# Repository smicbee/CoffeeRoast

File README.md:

# CoffeeRoast

We built a coffee roaster from a popcorn machine by adding temperature control. It follows a reproducible roast curve.

## Used Components

**Microcontroller:** LilyGo T-Display S3 ESP32-S3 (probably overkill, but it has a nice display and WiFi functionality if needed)  
From: [Amazon](https://www.amazon.de/LILYGO-T-Display-S3-Entwicklungsboard-Normalbildschirm-schwarzem/dp/B0BRTT727Z?source=ps-sl-shoppingads-lpcontext&ref_=fplfs&smid=ANWK9D8XV9DLB&th=1)

**Popcorn Maker:** [Severin Popcorn-Maker](https://popcorn-rezepte.de/severin-pc-3751-popcornautomat-weiss-heissluft)  
From: Ebay/Kleinanzeigen for 5-10€. People often get this as a gift, use it once or not at all, and then sell it on eBay.

**Temperature Sensor:** MAX6675 Temperature Sensor, K Type  
From: [Amazon](https://www.amazon.de/dp/B0DFM7SJ3Z?ref=ppx_yo2ov_dt_b_fed_asin_title)

**Solid State Relay:** Solid-State-Relay SSR-40DA  
From: [Amazon](https://www.amazon.de/dp/B0CDKCBJRT?ref=ppx_yo2ov_dt_b_fed_asin_title)

Cables, drills, screwdriver, soldering iron

## Instructions

To modify the roaster, we had to:
* Add a temperature sensor
* Add a solid-state relay to the heater
* Add a PWM transistor to the fan

First, we took apart the popcorn maker. It basically consists of two elements: heating coils and a fan for the air.  
These popcorn makers are engineered to the limit, so please be gentle with them as they are made of a lot of plastic. We destroyed a couple until we got it right. Even then, the plastic melted on the third continuous roast.

The main power switch connects the 230V from the outlet directly to the heating coils. The fan is connected to the heating coil in a way that ~24V AC goes through a rectifier (4 diodes) and is converted from AC to DC.

In the first step, we needed to decouple the heating coils from the fan and make the heating coil controllable using our solid-state relay. We disconnected the fan from the diodes so we could run it from an external power supply providing 24V later on.  
The heating coil was then soldered directly to the neutral conductor (blue wire). The red wire was cut, and the solid-state relay was installed in between so we could control the power of the heating element using PWM later.

An external or lab power supply was used to provide 24V DC to the fan, so it runs permanently. The fan can take from 4V to 30V. We can adjust the voltage to control the speed or later use a GPIO, a diode, and a transistor to control it from the ESP32. The ESP ensures a smooth start of the fan. We broke one of the fans due to rapid spin up/down.

We drilled a hole in the top metal container to fit the thermocouple inside the roasting chamber.  
**Note:** If the temperature sensor touches the metal casing, it won't work properly. We insulated the sensor with Kapton tape or a non-conductive washer. The temperature reading is 0°C if the motor is spinning and no insulation was used. This is handled by the code to be filtered out, but the roaster will go into fail-safe mode after 30s of nonsensical temperature readings and spin up the fan to 100%.

The other 4 pins go into the ESP32 (VCC = 5V, GND = Ground, CLK = GPIO_13, CS = GPIO_12, DO = GPIO_11).

Also, the solid-state relay is connected to the ESP32. In our case, the voltage provided by the GPIO was sufficient to control the solid-state relay, so we controlled it directly via the GPIO. If this does not work, you will need a separate transistor and a 5V supply for the SSR.  
The SSR uses GPIO_1 in our setup.

## Control Box

We 3D printed a box containing:
* ESP32
* 24V Fan PWM control
* SSR (solid-state relay) control
* Temperature sensor readout board

And that's it!

Initially, we wanted to use the ESP32 with Artisan (the software used for commercial products, e.g., Coffeelogic Nano), but we had no luck getting it to work with a PID. So, we decided to write our own software using C#. Communication is done via simple serial commands.  
You can send "get temp" via serial to the ESP32, and it will respond with the current temperature from the thermocouple.  
You can also send "set setpoint 255", which the ESP32 interprets to set the PWM duty cycle to 100% (255 = 100%, 128 = 50%, 0 = 0%).  
The firmware clamps `set setpoint` and `set fan` commands to the 0-255 PWM range and supports `get status` for a compact controller health line with state, temperature, heater, fan, fan target, and thermocouple error count.
The C# application can be found in the iRoastControl folder.

# Example Usage

Use no more than 100g of beans and roast in a well-ventilated area. Prepare for coffee skins flying _everywhere_.  
You can stop the roast at any time by flipping the on-off switch, which effectively disconnects the heater while keeping the cooling fan running.

[12s_roast.webm](https://github.com/user-attachments/assets/c60a7ab9-1068-4cd1-9d56-9880ee272cc1)

[12s video of 12min roasting](docu/assets/img/rel/12s_roast.webm)

# CoffeeRoast V2 Web

Die neue Steuerungsoberfläche liegt unter [`CoffeeRoast V2/`](CoffeeRoast%20V2/) und ist als moderne, responsive Webanwendung umgesetzt.

- Live-Verbindung zum bestehenden ESP32 über die Web Serial API
- vorhandenes serielles Protokoll und alle `.kpro`-Rezepte bleiben nutzbar
- Safety-Preflight, Failsafe, Vorheizen, Rösten und Abkühlen
- eingebauter Simulator, Canvas-Live-Plot und CSV-Export
- öffentlich bereitgestellt unter **https://coffeeroast.michaelbeetz.de/**

Für die USB-Verbindung wird Chrome oder Edge benötigt. Der Browser spricht direkt mit dem lokal ausgewählten USB-Gerät; der Webserver erhält keinen Zugriff auf den Controller.

# iRoastControl (Legacy)

iRoastControl is the control software. It comes with predefined roast curves you can use for your first roast.

## Build and Run on Windows

iRoastControl is a Windows Forms application for .NET Framework 4.7.2. Build it with Visual Studio 2022 and the ".NET desktop development" workload installed, including the .NET Framework 4.7.2 targeting pack or developer pack.

1. Connect the ESP32 roaster controller to the Windows PC over USB and confirm it appears as a COM port.
2. Open `iRoastControl Software/iRoastControl.sln` in Visual Studio.
3. Restore NuGet packages when Visual Studio prompts you, or use **Build > Restore NuGet Packages** before the first build. The project uses `packages.config`, so packages are restored into a repository-level `packages` folder.
4. Build the `Debug|Any CPU` or `Release|Any CPU` configuration, then press **Start** in Visual Studio or run the generated `iRoastControl.exe` from `iRoastControl Software/bin/Debug/` or `iRoastControl Software/bin/Release/`.

On startup the application scans available COM ports at `115200` baud, 8 data bits, no parity, one stop bit, and no handshake. It sends `hello` and expects the ESP32 firmware to answer `popcorn roaster`; after that it sends commands such as `get temp`, `set setpoint <0-255>`, and `set fan <0-255>`. If the app does not connect, check that the ESP32 firmware is running, no serial monitor has the port open, and the USB driver exposes the board as a COM port.

Roast recipes are loaded from the `Recipes` folder next to the running application. The source recipes live in `iRoastControl Software/Recipes/*.kpro` and are copied to the build output during the Visual Studio build. Add custom `.kpro` files to that folder before building, or copy them into `bin/Debug/Recipes/` or `bin/Release/Recipes/` beside the executable.

## First-Run Calibration and Safety Check

Before the first heated run, flash the ESP32 firmware, start iRoastControl, and leave the chamber empty. When you press "Run" from idle, the application requests `get status` from the controller and shows a preflight checklist. Confirm only after the thermocouple is insulated from the metal chamber, the fan moves air freely, the SSR is wired through the controller, ventilation is running, and the manual power cut-off is reachable.

Each roasting curve has three phases: pre-heating, running, and cool-down. When you click "Run" the first time, the application pre-heats the empty popcorn machine until the thermocouple reaches 180°C. This is when you add your coffee beans. After that, press "Run" again and the button will turn yellow. This is where the roasting curve starts. You can follow your roasting temperatures by watching the red graph. Pressing the "Run" button again will abort and start the cool-down phase, where the heating element turns off and only the fan runs. When the temperature drops below 60°C, the app returns to idle.

If the thermocouple returns repeated impossible readings, the firmware enters failsafe, turns the heater off, and drives the fan to 255/255. The app also treats a controller status containing `failsafe` as a blocked start until the wiring or sensor issue is fixed.

## UI

At the moment, the curves are defined by some points in the source code, which get interpolated using a CubicSpline function. You can find the key points in `ControlClass.cs` in the function `generateDefaultCurve()`. Each point describes the temperature depending on the time in seconds, e.g., `targetPoints.Add(new PointF(660, 180));` means at 660s of the roasting curve, we should reach 180°C.  
Adjust as you like.

# Fails

If the popcorn maker is old (like 20 years), the fan blades are rather brittle and may break easily if used on full power.

**Note:** If the temperature sensor touches the metal casing, it won't work properly. We recommend insulating the sensor with Kapton tape or a non-conductive washer.

# Tips

* Cover any holes on top with Kapton tape to retain heat better. Plastic might melt a bit, though.
* Test the roast with actual popcorn, as it's cheaper if anything goes wrong.
* Experiment and change only one setting at a time.

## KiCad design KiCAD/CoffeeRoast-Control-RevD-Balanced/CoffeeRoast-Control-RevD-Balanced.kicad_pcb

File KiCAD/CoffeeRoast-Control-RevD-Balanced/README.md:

# CoffeeRoast Control RevD Balanced — final routed candidate

RevD is a **separate final routed candidate** derived from the exact RevC UltraCompact circuit and footprints. It keeps the **96 × 60 mm, two-layer** board outline but distributes the functional blocks more evenly over the usable area.

The proven RevC project remains untouched.

## What changed

- Thermocouple/MAX6675 block moved upward and opened out.
- SSR and fan-driver support parts use more of the centre-left area instead of crowding the bottom edge.
- RESET/BOOT controls and probes have clearer service access.
- USB-C remains on the top edge. J5 is rotated 180° so the XKB `Product Edge`/mating face is exactly at board `y = 0`; the fine SMT tail row is inboard at `y = 7.345 mm`. Field wiring remains grouped along the bottom edge.
- ESP32-S3-WROOM-1 moved to the top edge; the physical antenna front is exactly flush with `y = 0`.
- The on-board antenna keepout is now **48 × 6.2 mm**: Espressif's 18 × 6.2 mm antenna area plus conservative 15 mm side clearances; forward clearance lies outside the PCB.
- Buck converter moved upward into the recovered right-hand area.
- SSR, ESC/PWM, fan and 24 V field pads are distributed farther apart along the bottom edge.
- Front and back silkscreen identify the functional blocks, including USB/ESD, MAX6675 thermocouple front-end, SSR driver, 10 V gate supply, fan driver/MOSFET, ESP32-S3, antenna keepout and 24 V-to-3.3 V buck stage.
- Three compact, unpopulated 1.27 mm headers reserve the future local user interface without changing firmware:
  - `J7` digital microphone: 3V3, GND, BCLK, WS, DATA, SEL;
  - `J8` I2C LCD: 3V3, GND, SDA, SCL, INT, RST;
  - `J9` four-button panel: GND, BTN1, BTN2, BTN3, BTN4, optional 3V3.
- All three future UI connectors are explicitly 3.3 V interfaces. They are hardware reservations only; pin initialization, I2S/I2C drivers, pull-ups and button handling are not implemented in software yet.
- J7–J9 now use horizontal pad rows. Every pin function is printed immediately beside its pad with 90-degree text on both board sides, and each complete MIC/LCD/BUTTONS group is enclosed by its own silkscreen frame.
- Board remains SELV/low voltage only; 230 VAC stays outside the PCB.

## Final verification state

RevD is fully routed as a reproducible two-layer manufacturing candidate:

- board outline: **96 × 60 mm**
- copper layers: **F.Cu + B.Cu only**
- full routed DRC: **0 violations**
- unconnected items: **0**
- schematic ERC: **0 violations**
- schematic/PCB parity: **0 issues**
- orientation/polarity audit: **PASS, 32 functional references asserted**
- routing angle audit: **0 non-45°/90° segments**
- `+24V_RAW` and `FAN_NEG`: **1.0 mm throughout, no vias**
- USB D+/D- total-length skew: **5.694 mm** (short USB Full-Speed path; electrically negligible timing skew)
- top/bottom/combined routing renders: `render/final-routing/`
- detailed audit: `docs/orientation_and_mechanical_audit.md`

The local fabrication package is generated under `production/partial-smd-pcba/` and contains Gerber, drill, BOM, CPL, DNP/HAND lists and zero-finding QA reports. It is locally order-ready, but checkout remains blocked until the live assembler preview confirms package identity, Pin 1/polarity, placement, current stock and enclosure fit.

## Reproduce and verify the final route

From this directory with KiCad/pcbnew 9.0.8:

```bash
python3 -m pip install -r tools/requirements.txt
python3 tools/add_ui_connectors_to_schematic.py
/usr/bin/python3 tools/build_balanced_revd.py
/usr/bin/python3 tools/finalize_routing.py
/usr/bin/python3 tools/audit_orientation_sensitive_parts.py
/usr/bin/python3 tools/audit_final_routing.py
kicad-cli pcb drc --severity-all --format json \
  --all-track-errors --schematic-parity \
  -o qa/placement-ui-parity-drc.json CoffeeRoast-Control-RevD-Balanced.kicad_pcb
kicad-cli sch erc --format json \
  -o qa/erc-ui.json CoffeeRoast-Control-RevD-Balanced.kicad_sch
/usr/bin/python3 tools/render_routing_preview.py
/usr/bin/python3 tools/prepare_partial_pcba_package.py
```

The final-routing script is idempotent by default once revision `D-FINAL` is present. Pass `--force` only for a deliberate full regeneration. It uses the SHA-256-pinned Freerouting 2.2.4 engine, pre-routes the fine-pitch USB VBUS and MCU-side D+ constraints, preserves 1.0 mm critical-current classes, removes exact SES duplicates, adds both GND planes and marks the result `D-FINAL`.

The detailed UI pin map, including physical pad coordinates, is in `docs/ui_expansion_connectors.csv`. The 1.27 mm headers remain `HAND/DNP` placeholders until the display, microphone module and enclosure cable scheme are selected.

## Electrical simulation

A reproducible block-level electrical simulation is in `sim/`. It covers the 24 V-to-3.3 V buck power stage, feedback corners, fan MOSFET loss, 10 V gate-supply budget, 24 V PSU loading, input bulk capacitance, USB CC current and an external SSR-input sweep. See `sim/README.md` for results and explicit model limits.

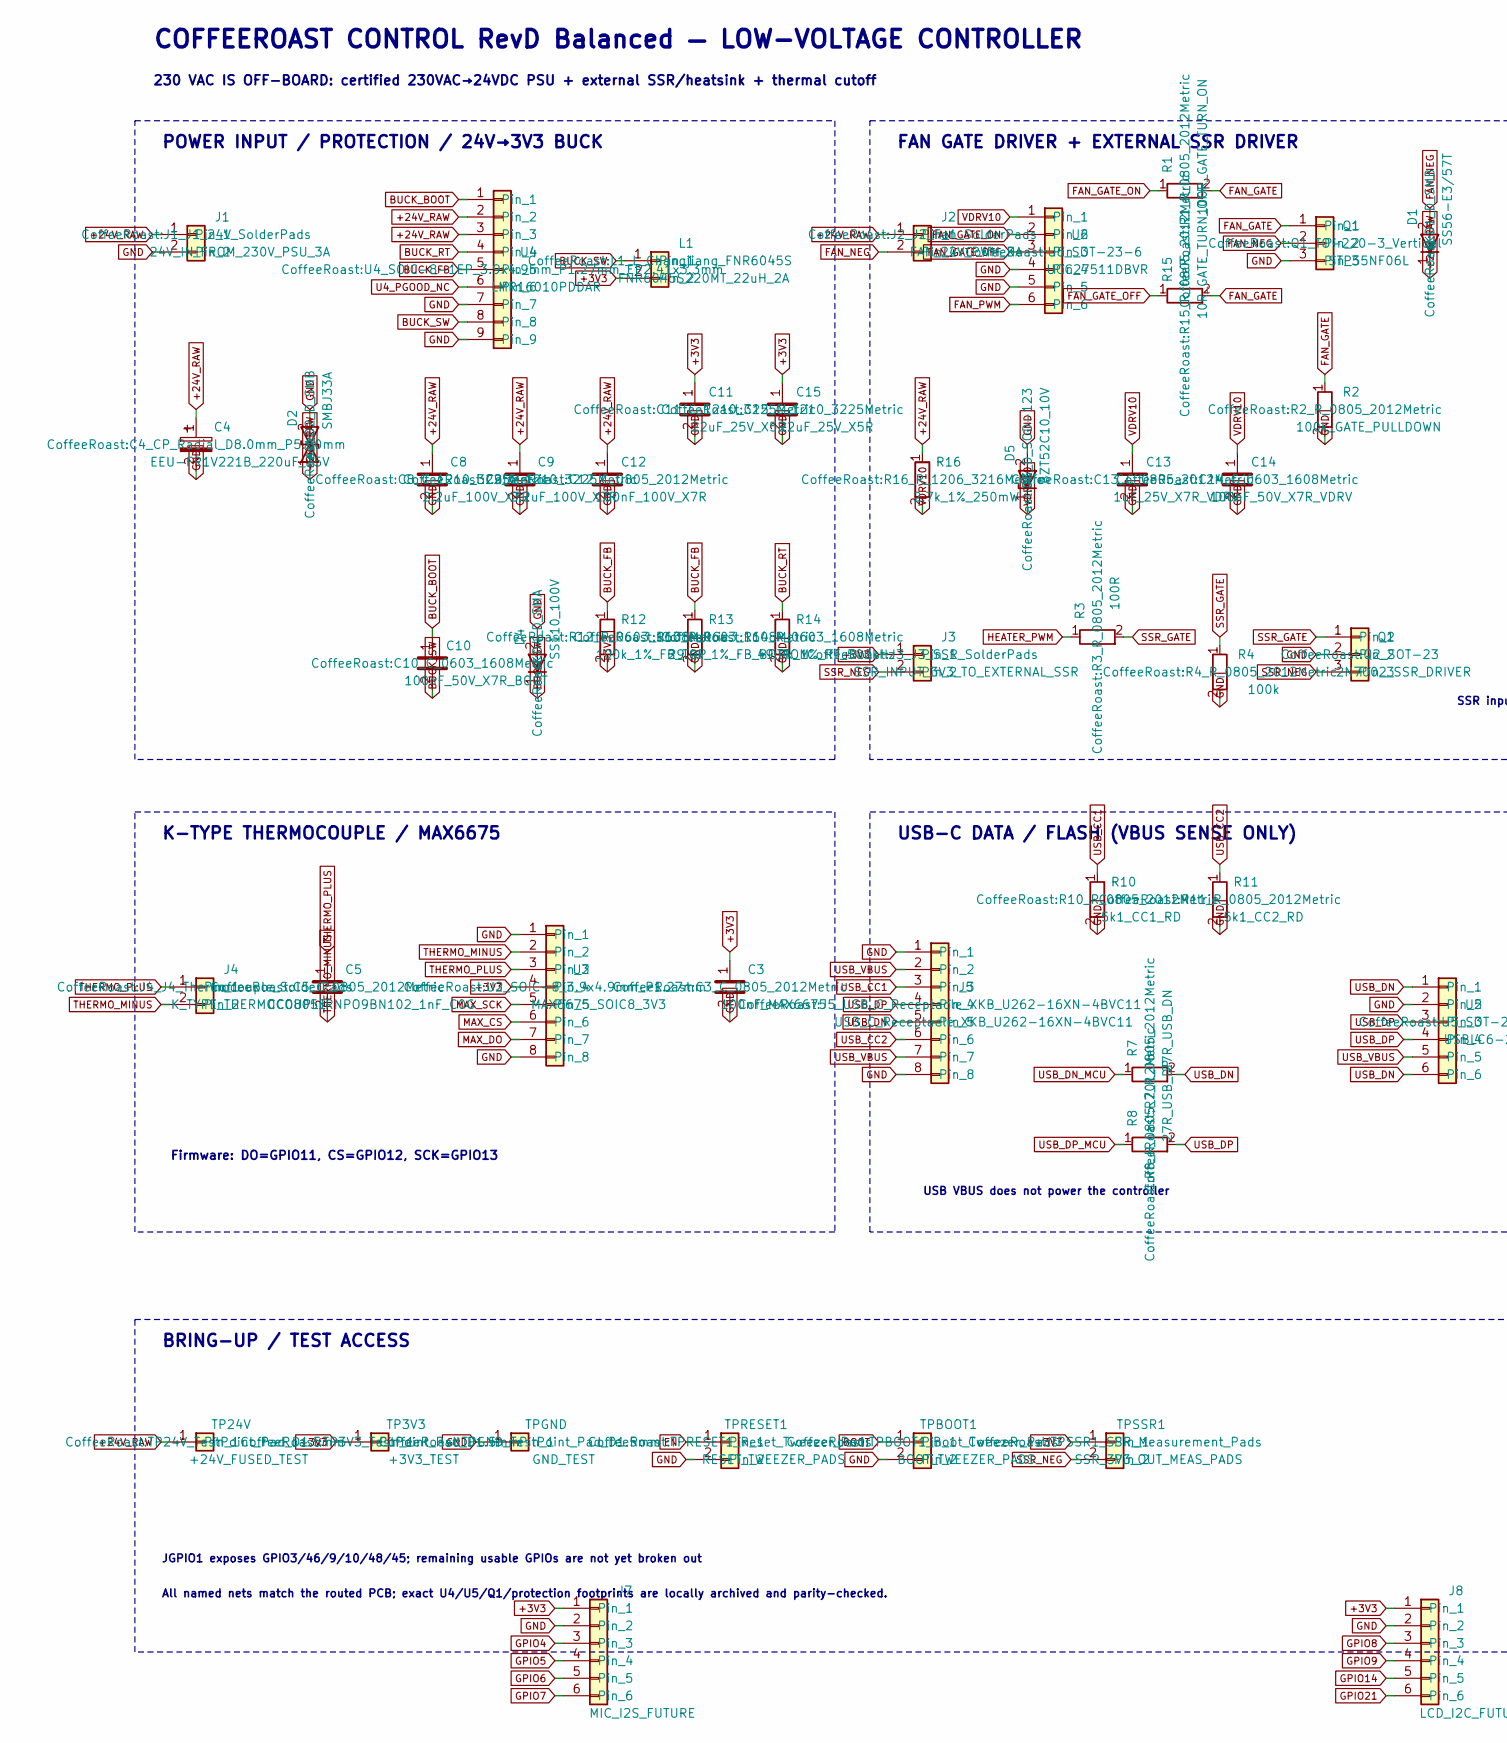
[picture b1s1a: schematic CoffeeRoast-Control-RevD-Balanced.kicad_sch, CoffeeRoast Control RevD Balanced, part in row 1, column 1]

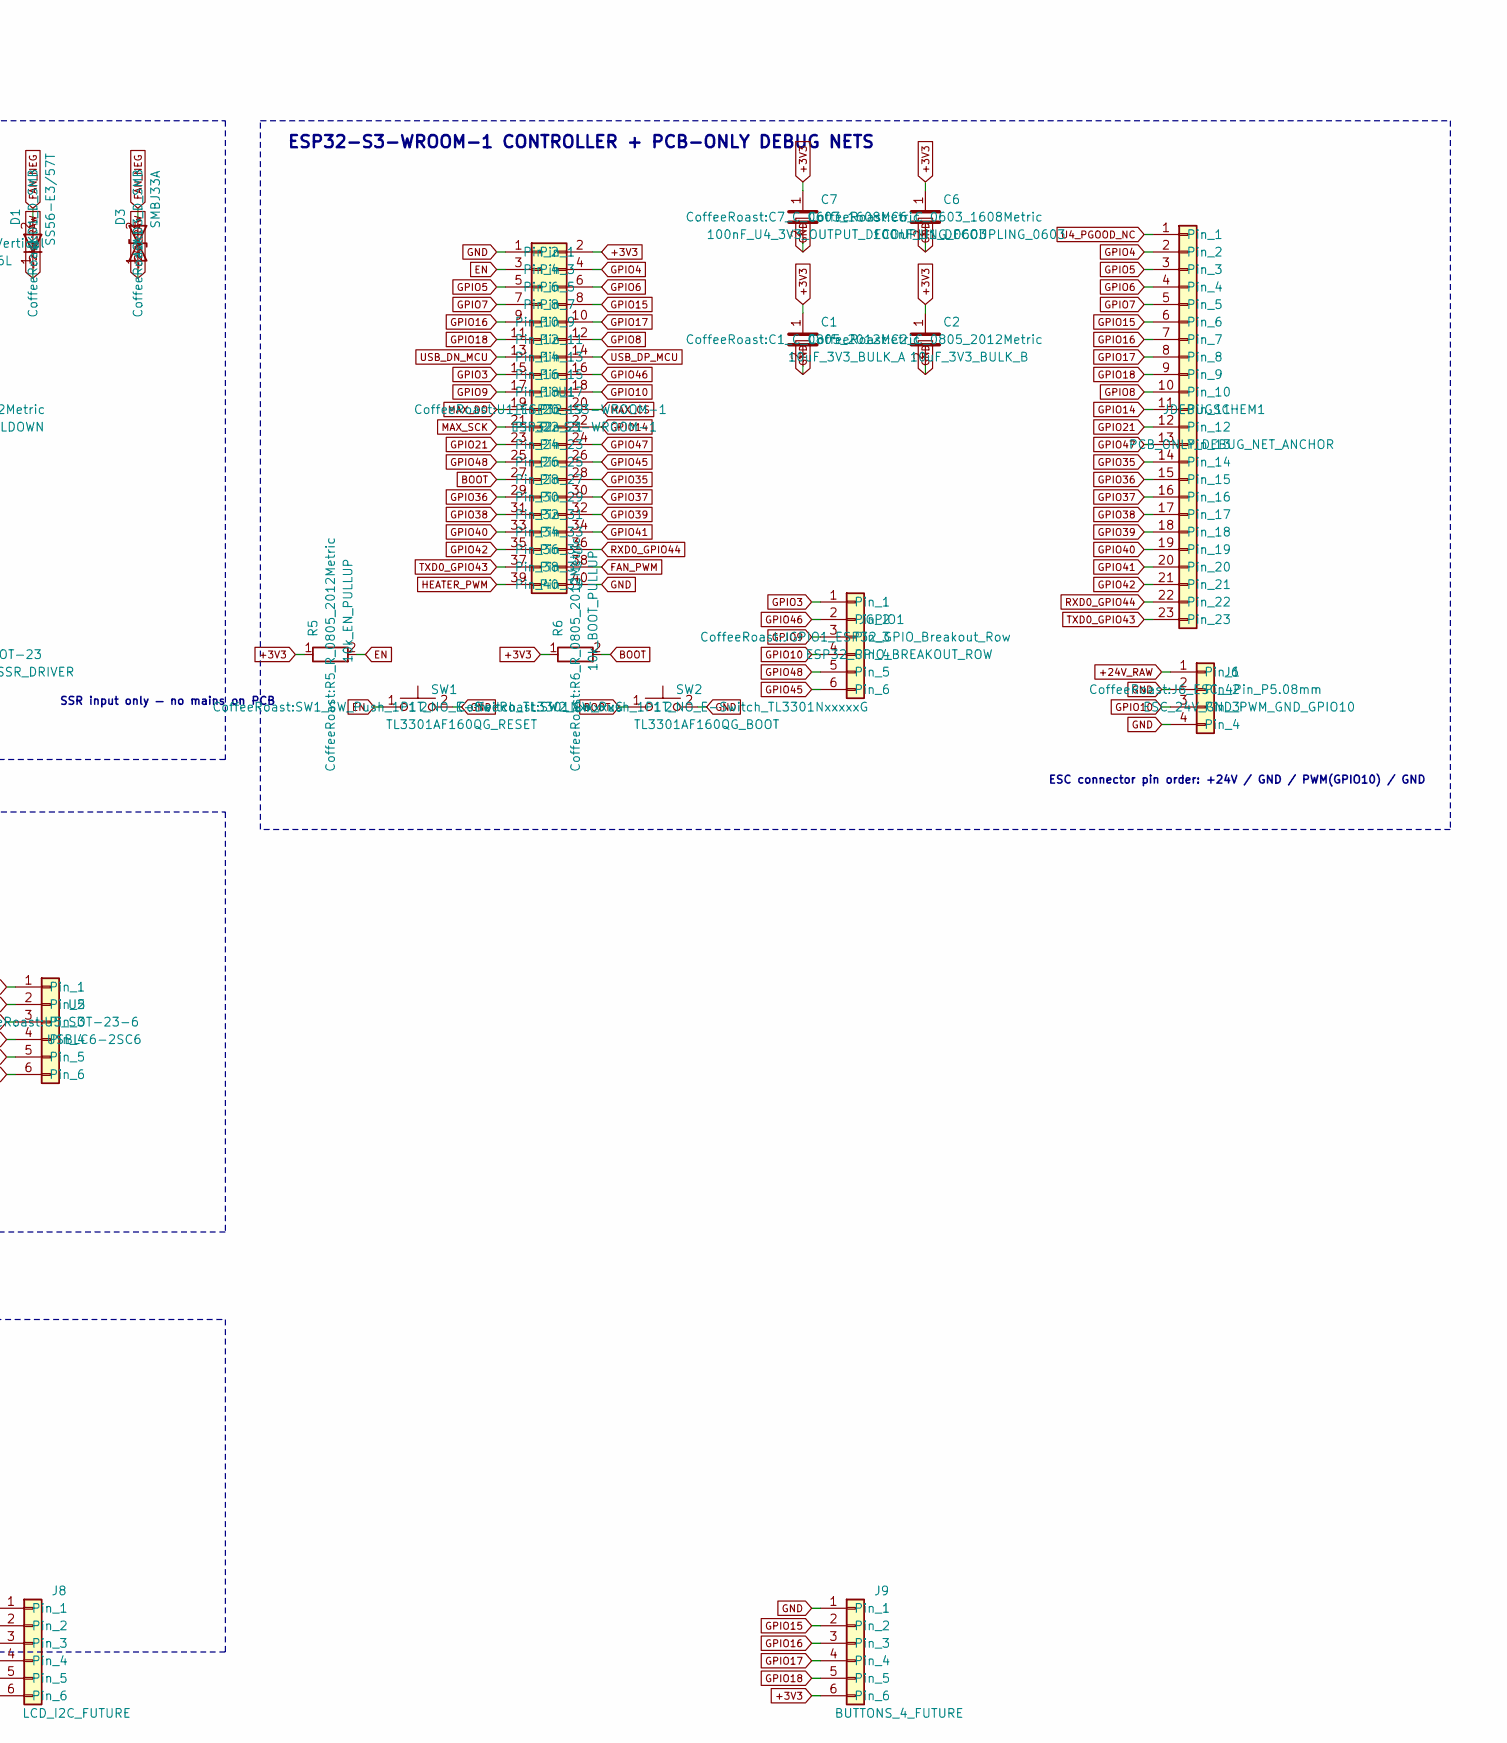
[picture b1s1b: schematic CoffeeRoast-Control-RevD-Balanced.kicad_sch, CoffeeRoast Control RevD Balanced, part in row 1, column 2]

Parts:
C1: 10uF_3V3_BULK_A; C1_C_0805_2012Metric
C2: 10uF_3V3_BULK_B; C2_C_0805_2012Metric
C3: 100nF_MAX6675; C3_C_0805_2012Metric
C4: EEU-FR1V221B_220uF_35V; C4_CP_Radial_D8.0mm_P5.00mm
C5: CC0805JRNPO9BN102_1nF_C0G; C5_C_0805_2012Metric
C6: 100nF_U1_DECOUPLING_0603; C6_C_0603_1608Metric
C7: 100nF_U4_3V3_OUTPUT_DECOUPLING_0603; C7_C_0603_1608Metric
C8: 2.2uF_100V_X7R; C8_C_1210_3225Metric
C9: 2.2uF_100V_X7R; C9_C_1210_3225Metric
C10: 100nF_50V_X7R_BOOT; C10_C_0603_1608Metric
C11: 22uF_25V_X5R; C11_C_1210_3225Metric
C12: 100nF_100V_X7R; C12_C_0805_2012Metric
C13: 1uF_25V_X7R_VDRV; C13_C_0805_2012Metric
C14: 100nF_50V_X7R_VDRV; C14_C_0603_1608Metric
C15: 22uF_25V_X5R; C15_C_1210_3225Metric
D1: SS56-E3/57T; D1_D_SMB
D2: SMBJ33A; D2_D_SMB
D3: SMBJ33A; D3_D_SMB
D4: SS110_100V; D4_D_SMA
D5: BZT52C10_10V; D5_D_SOD-123
J1: 24V_IN_FROM_230V_PSU_3A; J1_J1_24V_SolderPads
J2: FAN_24V_PWM_3A; J2_J2_Fan_SolderPads
J3: SSR_INPUT_3V3_TO_EXTERNAL_SSR; J3_J3_SSR_SolderPads
J4: K_TYPE_THERMOCOUPLE; J4_J4_Thermocouple_SolderPads
J5: USB_C_Receptacle_XKB_U262-16XN-4BVC11; J5_USB_C_Receptacle_XKB_U262-16XN-4BVC11
J6: ESC_24V_GND_PWM_GND_GPIO10; J6_ESC_4Pin_P5.08mm
J7: MIC_I2S_FUTURE; PinHeader_1x06_P1.27mm_Vertical
J8: LCD_I2C_FUTURE; PinHeader_1x06_P1.27mm_Vertical
J9: BUTTONS_4_FUTURE; PinHeader_1x06_P1.27mm_Vertical
JDEBUGSCHEM1: PCB_ONLY_DEBUG_NET_ANCHOR
JGPIO1: ESP32_GPIO_BREAKOUT_ROW; JGPIO1_ESP32_GPIO_Breakout_Row
L1: FNR6045S220MT_22uH_2A; L1_L_Changjiang_FNR6045S
Q1: STP55NF06L; Q1_TO-220-3_Vertical
Q2: 2N7002_SSR_DRIVER; Q2_SOT-23
R1: 100R_GATE_TURN_ON; R1_R_0805_2012Metric
R2: 100k_GATE_PULLDOWN; R2_R_0805_2012Metric
R3: 100R; R3_R_0805_2012Metric
R4: 100k; R4_R_0805_2012Metric
R5: 10k_EN_PULLUP; R5_R_0805_2012Metric
R6: 10k_BOOT_PULLUP; R6_R_0805_2012Metric
R7: 27R_USB_DN; R7_R_0805_2012Metric
R8: 27R_USB_DP; R8_R_0805_2012Metric
R10: 5k1_CC1_RD; R10_R_0805_2012Metric
R11: 5k1_CC2_RD; R11_R_0805_2012Metric
R12: 100k_1%_FB_TOP; R12_R_0603_1608Metric
R13: 29.4k_1%_FB_BOTTOM; R13_R_0603_1608Metric
R14: 49.9k_1%_RT_500kHz; R14_R_0603_1608Metric
R15: 10R_GATE_TURN_OFF; R15_R_0805_2012Metric
R16: 2.7k_1%_250mW; R16_R_1206_3216Metric
SW1: TL3301AF160QG_RESET; SW1_SW_Push_1P1T_NO_E-Switch_TL3301NxxxxxG
SW2: TL3301AF160QG_BOOT; SW2_SW_Push_1P1T_NO_E-Switch_TL3301NxxxxxG
TP3V3: +3V3_TEST; TP3V3_TestPoint_Pad_D1.5mm
TP24V: +24V_FUSED_TEST; TP24V_TestPoint_Pad_D1.5mm
TPBOOT1: BOOT_TWEEZER_PADS; TPBOOT1_Boot_Tweezer_Pads
TPGND: GND_TEST; TPGND_TestPoint_Pad_D1.5mm
TPRESET1: RESET_TWEEZER_PADS; TPRESET1_Reset_Tweezer_Pads
TPSSR1: SSR_3V3_OUT_MEAS_PADS; TPSSR1_SSR_Measurement_Pads
U1: ESP32-S3-WROOM-1; U1_ESP32-S3-WROOM-1
U2: MAX6675_SOIC8_3V3; U2_SOIC-8_3.9x4.9mm_P1.27mm
U4: LMR16010PDDAR; U4_SOIC-8-1EP_3.9x4.9mm_P1.27mm_EP2.41x3.3mm
U5: USBLC6-2SC6; U5_SOT-23-6
U6: UCC27511DBVR; U6_SOT-23-6

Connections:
+3V3: C1.1, C2.1, C3.1, C6.1, C7.1, C11.1, C15.1, J3.1, J7.1, J8.1, J9.6, L1.2, R5.1, R6.1, R12.2, TP3V3.1, TPSSR1.1, U1.2, U2.4
+24V_RAW: C4.1, C8.1, C9.1, C12.1, D1.1 (K), D2.1 (A1), D3.1 (A1), J1.1, J2.1, J6.1, R16.1, TP24V.1, U4.2, U4.3
BOOT: R6.2, SW2.1, TPBOOT1.1, U1.27
BUCK_BOOT: C10.1, U4.1
BUCK_FB: R12.1, R13.1, U4.5
BUCK_RT: R14.1, U4.4
BUCK_SW: C10.2, D4.1 (K), L1.1, U4.8
EN: R5.2, SW1.1, TPRESET1.1, U1.3
FAN_GATE: Q1.1, R1.2, R2.1, R15.2
FAN_GATE_OFF: R15.1, U6.3
FAN_GATE_ON: R1.1, U6.2
FAN_NEG: D1.2 (A), D3.2 (A2), J2.2, Q1.2
FAN_PWM: U1.38, U6.6
GND: C1.2, C2.2, C3.2, C4.2, C6.2, C7.2, C8.2, C9.2, C11.2, C12.2, C13.2, C14.2, C15.2, D2.2 (A2), D4.2 (A), D5.2 (A), J1.2, J5.1, J5.8, J6.2, J6.4, J7.2, J8.2, J9.1, Q1.3, Q2.2, R2.2, R4.2, R10.2, R11.2, R13.2, R14.2, SW1.2, SW2.2, TPBOOT1.2, TPGND.1, TPRESET1.2, U1.1, U1.40, U2.1, U2.8, U4.7, U4.9, U5.2, U6.4, U6.5
GPIO3: JGPIO1.1, U1.15
GPIO4: J7.3, JDEBUGSCHEM1.2, U1.4
GPIO5: J7.4, JDEBUGSCHEM1.3, U1.5
GPIO6: J7.5, JDEBUGSCHEM1.4, U1.6
GPIO7: J7.6, JDEBUGSCHEM1.5, U1.7
GPIO8: J8.3, JDEBUGSCHEM1.10, U1.12
GPIO9: J8.4, JGPIO1.3, U1.17
GPIO10: J6.3, JGPIO1.4, U1.18
GPIO14: J8.5, JDEBUGSCHEM1.11, U1.22
GPIO15: J9.2, JDEBUGSCHEM1.6, U1.8
GPIO16: J9.3, JDEBUGSCHEM1.7, U1.9
GPIO17: J9.4, JDEBUGSCHEM1.8, U1.10
GPIO18: J9.5, JDEBUGSCHEM1.9, U1.11
GPIO21: J8.6, JDEBUGSCHEM1.12, U1.23
GPIO35: JDEBUGSCHEM1.14, U1.28
GPIO36: JDEBUGSCHEM1.15, U1.29
GPIO37: JDEBUGSCHEM1.16, U1.30
GPIO38: JDEBUGSCHEM1.17, U1.31
GPIO39: JDEBUGSCHEM1.18, U1.32
GPIO40: JDEBUGSCHEM1.19, U1.33
GPIO41: JDEBUGSCHEM1.20, U1.34
GPIO42: JDEBUGSCHEM1.21, U1.35
GPIO45: JGPIO1.6, U1.26
GPIO46: JGPIO1.2, U1.16
GPIO47: JDEBUGSCHEM1.13, U1.24
GPIO48: JGPIO1.5, U1.25
HEATER_PWM: R3.1, U1.39
MAX_CS: U1.20, U2.6
MAX_DO: U1.19, U2.7
MAX_SCK: U1.21, U2.5
RXD0_GPIO44: JDEBUGSCHEM1.22, U1.36
SSR_GATE: Q2.1, R3.2, R4.1
SSR_NEG: J3.2, Q2.3, TPSSR1.2
THERMO_MINUS: C5.2, J4.2, U2.2
THERMO_PLUS: C5.1, J4.1, U2.3
TXD0_GPIO43: JDEBUGSCHEM1.23, U1.37
U4_PGOOD_NC: JDEBUGSCHEM1.1, U4.6
USB_CC1: J5.3, R10.1
USB_CC2: J5.6, R11.1
USB_DN: J5.5, R7.2, U5.1, U5.6
USB_DN_MCU: R7.1, U1.13
USB_DP: J5.4, R8.2, U5.3, U5.4
USB_DP_MCU: R8.1, U1.14
USB_VBUS: J5.2, J5.7, U5.5
VDRV10: C13.1, C14.1, D5.1 (K), R16.2, U6.1

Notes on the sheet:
Firmware: DO=GPIO11, CS=GPIO12, SCK=GPIO13
230 VAC IS OFF-BOARD: certified 230VAC→24VDC PSU + external SSR/heatsink + thermal cutoff
All named nets match the routed PCB; exact U4/U5/Q1/protection footprints are locally archived and parity-checked.
JGPIO1 exposes GPIO3/46/9/10/48/45; remaining usable GPIOs are not yet broken out
POWER INPUT / PROTECTION / 24V→3V3 BUCK
SSR input only — no mains on PCB
COFFEEROAST CONTROL RevD Balanced — LOW-VOLTAGE CONTROLLER
USB VBUS does not power the controller
FAN GATE DRIVER + EXTERNAL SSR DRIVER
ESP32-S3-WROOM-1 CONTROLLER + PCB-ONLY DEBUG NETS
BRING-UP / TEST ACCESS
USB-C DATA / FLASH (VBUS SENSE ONLY)
K-TYPE THERMOCOUPLE / MAX6675
ESC connector pin order: +24V / GND / PWM(GPIO10) / GND

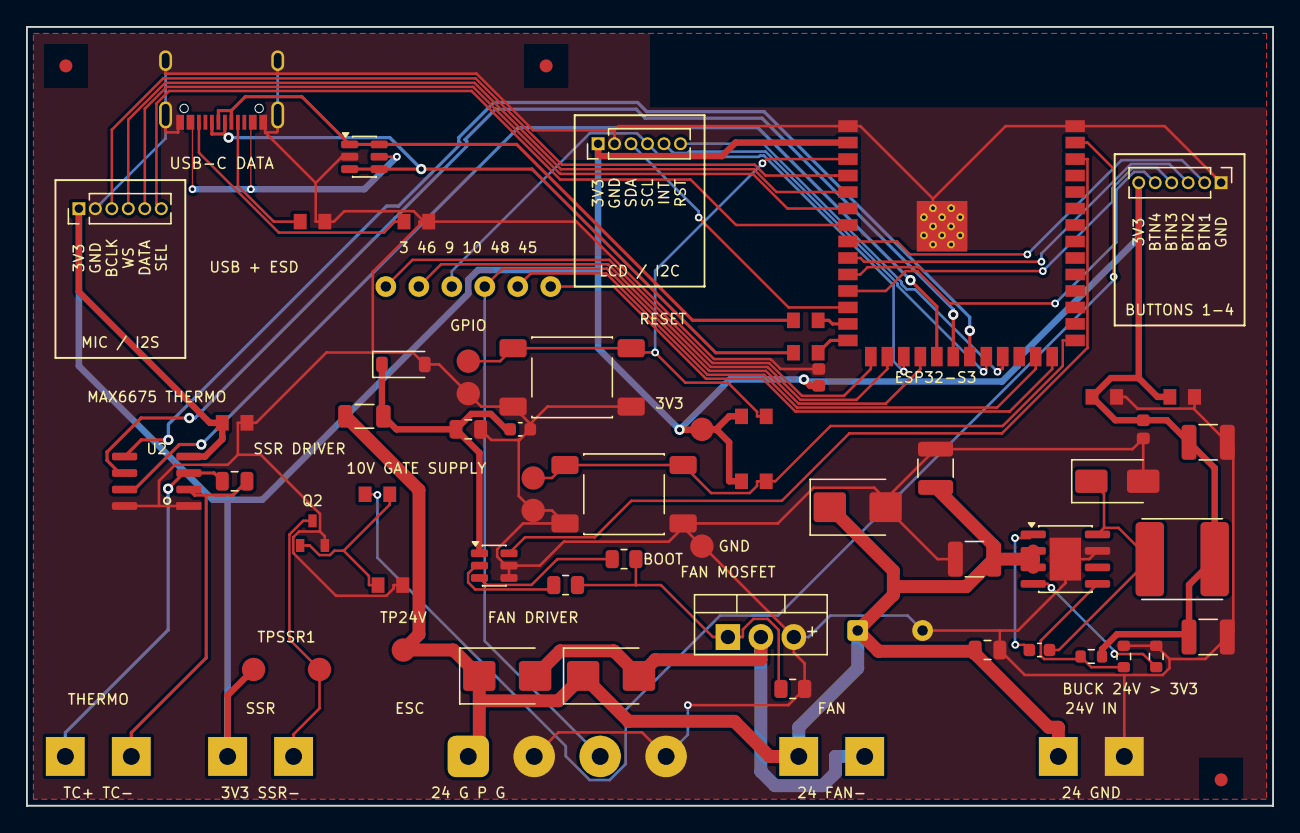
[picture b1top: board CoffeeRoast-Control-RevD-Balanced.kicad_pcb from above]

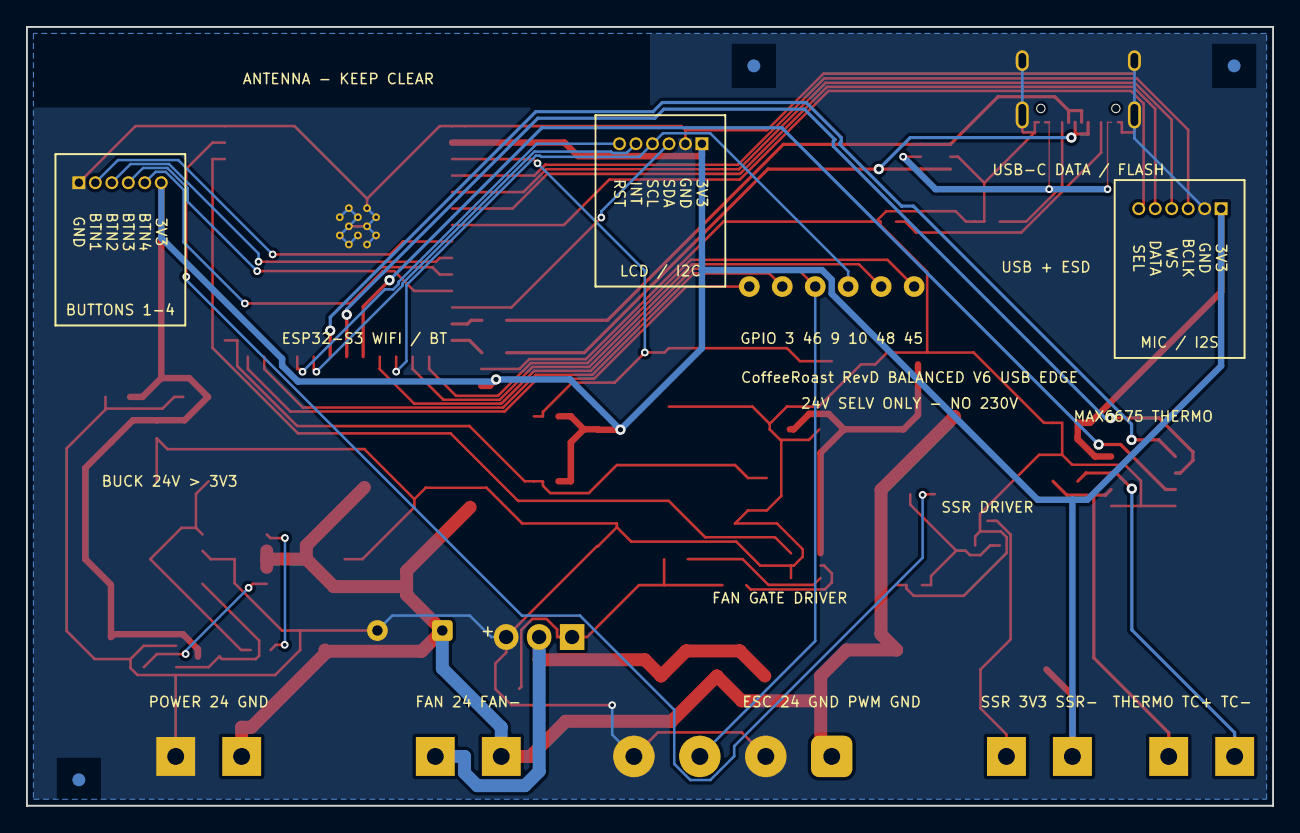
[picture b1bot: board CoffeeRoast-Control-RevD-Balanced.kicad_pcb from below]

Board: 2 copper layers, 96.0 x 60.0 mm, 67 parts (3 on the bottom side), 47 nets.

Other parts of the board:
FID1: FIDUCIAL_GLOBAL_1MM; FID1_Fiducial_1mm_Mask2mm
FID2: FIDUCIAL_GLOBAL_1MM; FID2_Fiducial_1mm_Mask2mm
FID3: FIDUCIAL_GLOBAL_1MM; FID3_Fiducial_1mm_Mask2mm
FID4: FIDUCIAL_GLOBAL_1MM; FID4_Fiducial_1mm_Mask2mm
FID5: FIDUCIAL_GLOBAL_1MM; FID5_Fiducial_1mm_Mask2mm
FID6: FIDUCIAL_GLOBAL_1MM; FID6_Fiducial_1mm_Mask2mm

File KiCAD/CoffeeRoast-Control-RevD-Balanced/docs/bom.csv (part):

Ref,Qty,Value/Part,Footprint,Manufacturer Part,Supplier Part,Assembly,Notes
C1,1,10uF_3V3_BULK_A,CoffeeRoast:C1_C_0805_2012Metric,GRM21BR61E106KA73L,C84416,PCBA,10uF 25V X5R 3V3 bulk A.
C2,1,10uF_3V3_BULK_B,CoffeeRoast:C2_C_0805_2012Metric,GRM21BR61E106KA73L,C84416,PCBA,10uF 25V X5R 3V3 bulk B.
C3,1,100nF_MAX6675,CoffeeRoast:C3_C_0805_2012Metric,CC0805KRX7R9BB104,C49678,PCBA,100nF MAX6675 decoupling.
C4,1,EEU-FR1V221B_220uF_35V,CoffeeRoast:C4_CP_Radial_D8.0mm_P5.00mm,EEU-FR1V221B,C1583130,HAND/DNP,Panasonic EEU-FR1V221B 220uF/35V radial electrolytic; hand-solder and observe polarity.
C5,1,CC0805JRNPO9BN102_1nF_C0G,CoffeeRoast:C5_C_0805_2012Metric,CC0805JRNPO9BN102,C62774,DNP,Optional CC0805JRNPO9BN102 1nF C0G thermocouple filter; DNP until noise/bias testing confirms it.
C6,1,100nF_U1_DECOUPLING_0603,CoffeeRoast:C6_C_0603_1608Metric,CC0603KRX7R9BB104,C14663,PCBA,100nF ESP32 decoupling.
C7,1,100nF_U4_3V3_OUTPUT_DECOUPLING_0603,CoffeeRoast:C7_C_0603_1608Metric,CC0603KRX7R9BB104,C14663,PCBA,100nF 3V3 output decoupling.
C8,1,2.2uF_100V_X7R,CoffeeRoast:C8_C_1210_3225Metric,CS3225X7R225K101NRK,C2900749,PCBA,2.2uF 100V buck input.
C9,1,2.2uF_100V_X7R,CoffeeRoast:C9_C_1210_3225Metric,CS3225X7R225K101NRK,C2900749,PCBA,2.2uF 100V buck input.
C10,1,100nF_50V_X7R_BOOT,CoffeeRoast:C10_C_0603_1608Metric,CC0603KRX7R9BB104,C14663,PCBA,100nF bootstrap.
C11,1,22uF_25V_X5R,CoffeeRoast:C11_C_1210_3225Metric,CL32A226KAJNNNE,C52306,PCBA,22uF 25V buck output.
C12,1,100nF_100V_X7R,CoffeeRoast:C12_C_0805_2012Metric,0805B104K101NT,C89258,PCBA,100nF 100V buck input HF bypass.
C13,1,1uF_25V_X7R_VDRV,CoffeeRoast:C13_C_0805_2012Metric,CL21B105KAFNNNE,C116352,PCBA,1uF VDRV reservoir.
C14,1,100nF_50V_X7R_VDRV,CoffeeRoast:C14_C_0603_1608Metric,CC0603KRX7R9BB104,C14663,PCBA,100nF VDRV bypass.
C15,1,22uF_25V_X5R,CoffeeRoast:C15_C_1210_3225Metric,CL32A226KAJNNNE,C52306,PCBA,22uF 25V buck output.
D1,1,SS56-E3/57T,CoffeeRoast:D1_D_SMB,SS56-E3/57T,,HAND/DNP,"Vishay SS56-E3/57T SMB flyback diode; exact pad/polarity validated, hand-solder because assembler mapping is not pre-filled."
D2,1,SMBJ33A,CoffeeRoast:D2_D_SMB,SMBJ33A-13-F,C135067,PCBA,24V input TVS; cathode/pad 1 to +24V_RAW.
D3,1,SMBJ33A,CoffeeRoast:D3_D_SMB,SMBJ33A-13-F,C135067,PCBA,Fan TVS; cathode/pad 1 to +24V_RAW.
D4,1,SS110_100V,CoffeeRoast:D4_D_SMA,SS110,C2766060,PCBA,100V buck catch diode.
D5,1,BZT52C10_10V,CoffeeRoast:D5_D_SOD-123,BZT52C10,C49023497,PCBA,10V VDRV clamp.
J1,1,24V_IN_FROM_230V_PSU_3A,CoffeeRoast:J1_J1_24V_SolderPads,24V_IN_FROM_230V_PSU_3A,,HAND/DNP,Large plated hand-solder pads; solder PSU leads and add strain relief.
J2,1,FAN_24V_PWM_3A,CoffeeRoast:J2_J2_Fan_SolderPads,FAN_24V_PWM_3A,,HAND/DNP,Large plated hand-solder pads; solder fan leads and add strain relief.
J3,1,SSR_INPUT_3V3_TO_EXTERNAL_SSR,CoffeeRoast:J3_J3_SSR_SolderPads,SSR_INPUT_3V3_TO_EXTERNAL_SSR,,HAND/DNP,Large plated hand-solder pads; solder external SSR control leads.
J4,1,K_TYPE_THERMOCOUPLE,CoffeeRoast:J4_J4_Thermocouple_SolderPads,K_TYPE_THERMOCOUPLE,,HAND/DNP,Large plated hand-solder pads; solder thermocouple extension leads and add strain relief.
J5,1,USB_C_Receptacle_XKB_U262-16XN-4BVC11,CoffeeRoast:J5_USB_C_Receptacle_XKB_U262-16XN-4BVC11,U262-16 1 N-4BVC11,C319148,PCBA,Verify shell and pin orientation in placement preview.
J6,1,ESC_24V_GND_PWM_GND_GPIO10,CoffeeRoast:J6_ESC_4Pin_P5.08mm,ESC_4PIN_HAND_WIRE,,HAND/DNP,"Four large hand-solder pads for ESC: +24V, GND, PWM (GPIO10), GND; add strain relief."
J7,1,MIC_I2S_FUTURE,Connector_PinHeader_1.27mm:PinHeader_1x06_P1.27mm_Vertical,MIC_I2S_FUTURE,,HAND/DNP,Future 3.3V digital microphone header; HAND/DNP until module and cable mechanics are selected.
J8,1,LCD_I2C_FUTURE,Connector_PinHeader_1.27mm:PinHeader_1x06_P1.27mm_Vertical,LCD_I2C_FUTURE,,HAND/DNP,"Future 3.3V I2C LCD header; HAND/DNP until display, pull-ups and enclosure mechanics are selected."
J9,1,BUTTONS_4_FUTURE,Connector_PinHeader_1.27mm:PinHeader_1x06_P1.27mm_Vertical,BUTTONS_4_FUTURE,,HAND/DNP,Future four-button panel header; HAND/DNP until panel and enclosure mechanics are selected.
JGPIO1,1,ESP32_GPIO_BREAKOUT_ROW,CoffeeRoast:JGPIO1_ESP32_GPIO_Breakout_Row,ESP32_GPIO_BREAKOUT_ROW,,HAND/DNP,PCB test/debug/mechanical position; no automated placement.
L1,1,FNR6045S220MT_22uH_2A,CoffeeRoast:L1_L_Changjiang_FNR6045S,FNR6045S220MT,C168080,PCBA,"22uH, >=2A saturation/current candidate."
Q1,1,STP55NF06L,CoffeeRoast:Q1_TO-220-3_Vertical,STP55NF06L,C77582,PCBA,MANDATORY manufacturer-installed THT fan MOSFET; pins 1/2/3 are Gate/Drain/Source. Do not omit from PCBA; thermally validate at 2.5A fan current.
Q2,1,2N7002_SSR_DRIVER,CoffeeRoast:Q2_SOT-23,2N7002,C916396,PCBA,SSR low-side driver.
R1,1,100R_GATE_TURN_ON,CoffeeRoast:R1_R_0805_2012Metric,FRC0805F1000TS,C2907218,PCBA,100R fan gate turn-on.
R2,1,100k_GATE_PULLDOWN,CoffeeRoast:R2_R_0805_2012Metric,FRC0805F1003TS,C2907217,PCBA,100k fan gate pulldown.
R3,1,100R,CoffeeRoast:R3_R_0805_2012Metric,FRC0805F1000TS,C2907218,PCBA,100R SSR gate resistor.
R4,1,100k,CoffeeRoast:R4_R_0805_2012Metric,FRC0805F1003TS,C2907217,PCBA,100k SSR gate pulldown.
R5,1,10k_EN_PULLUP,CoffeeRoast:R5_R_0805_2012Metric,FRC0805F1002TS,C2907219,PCBA,10k EN pullup.
R6,1,10k_BOOT_PULLUP,CoffeeRoast:R6_R_0805_2012Metric,FRC0805F1002TS,C2907219,PCBA,10k BOOT pullup.
R7,1,27R_USB_DN,CoffeeRoast:R7_R_0805_2012Metric,0805W8F270JT5E,C17594,PCBA,27R USB D- series.
R8,1,27R_USB_DP,CoffeeRoast:R8_R_0805_2012Metric,0805W8F270JT5E,C17594,PCBA,27R USB D+ series.
R10,1,5k1_CC1_RD,CoffeeRoast:R10_R_0805_2012Metric,0805W8F5101T5E,C27834,PCBA,5.1k USB CC1 Rd.
R11,1,5k1_CC2_RD,CoffeeRoast:R11_R_0805_2012Metric,0805W8F5101T5E,C27834,PCBA,5.1k USB CC2 Rd.
R12,1,100k_1%_FB_TOP,CoffeeRoast:R12_R_0603_1608Metric,FRC0603F1003TS,C2906980,PCBA,100k FB top.
R13,1,29.4k_1%_FB_BOTTOM,CoffeeRoast:R13_R_0603_1608Metric,RC0603FR-0729K4L,C137752,PCBA,29.4k FB bottom.
R14,1,49.9k_1%_RT_500kHz,CoffeeRoast:R14_R_0603_1608Metric,RC0603FR-0749K9L,C114624,PCBA,"49.9k RT, about 500kHz."
R15,1,10R_GATE_TURN_OFF,CoffeeRoast:R15_R_0805_2012Metric,RC0805FR-0710RL,C96347,PCBA,10R fan gate turn-off.
R16,1,2.7k_1%_250mW,CoffeeRoast:R16_R_1206_3216Metric,1206W4F2701T5E,C17950,PCBA,"2.7k VDRV feed, 1%, 0.25W."
SW1,1,TL3301AF160QG_RESET,CoffeeRoast:SW1_SW_Push_1P1T_NO_E-Switch_TL3301NxxxxxG,TL3301AF160QG,C273519,PCBA,RESET switch; JLC model requires 90-degree CPL rotation so pins 1/2 and 3/4 land on the two board pad rows.
SW2,1,TL3301AF160QG_BOOT,CoffeeRoast:SW2_SW_Push_1P1T_NO_E-Switch_TL3301NxxxxxG,TL3301AF160QG,C273519,PCBA,BOOT switch; JLC model requires 90-degree CPL rotation so pins 1/2 and 3/4 land on the two board pad rows.
TPBOOT1,1,BOOT_TWEEZER_PADS,CoffeeRoast:TPBOOT1_Boot_Tweezer_Pads,BOOT_TWEEZER_PADS,,DNP,PCB test/debug/mechanical position; no automated placement.
TPGND,1,GND_TEST,CoffeeRoast:TPGND_TestPoint_Pad_D1.5mm,GND_TEST,,DNP,PCB test/debug/mechanical position; no automated placement.
TPRESET1,1,RESET_TWEEZER_PADS,CoffeeRoast:TPRESET1_Reset_Tweezer_Pads,RESET_TWEEZER_PADS,,DNP,PCB test/debug/mechanical position; no automated placement.
TPSSR1,1,SSR_3V3_OUT_MEAS_PADS,CoffeeRoast:TPSSR1_SSR_Measurement_Pads,SSR_3V3_OUT_MEAS_PADS,,DNP,PCB test/debug/mechanical position; no automated placement.
TP24V,1,+24V_FUSED_TEST,CoffeeRoast:TP24V_TestPoint_Pad_D1.5mm,+24V_FUSED_TEST,,DNP,PCB test/debug/mechanical position; no automated placement.
TP3V3,1,+3V3_TEST,CoffeeRoast:TP3V3_TestPoint_Pad_D1.5mm,+3V3_TEST,,DNP,PCB test/debug/mechanical position; no automated placement.
U1,1,ESP32-S3-WROOM-1,CoffeeRoast:U1_ESP32-S3-WROOM-1,ESP32-S3-WROOM-1-N8R8,C2913201,PCBA,Confirm N8R8 variant and antenna keepout.
U2,1,MAX6675_SOIC8_3V3,CoffeeRoast:U2_SOIC-8_3.9x4.9mm_P1.27mm,MAX6675ISA+T,C16030,PCBA,3.3V thermocouple converter.
U4,1,LMR16010PDDAR,CoffeeRoast:U4_SOIC-8-1EP_3.9x4.9mm_P1.27mm_EP2.41x3.3mm,LMR16010PDDAR,C183084,PCBA,60V/1A buck; verify Pin 1 and exposed-pad orientation.
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
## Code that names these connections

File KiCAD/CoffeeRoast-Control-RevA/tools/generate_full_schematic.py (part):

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two_pin_v("Device:C","C8","2.2uF_100V_X7R",2200,3000,"+24V_RAW","GND")
two_pin_v("Device:C","C9","2.2uF_100V_X7R",2700,3000,"+24V_RAW","GND")
two_pin_v("Device:C","C12","100nF_100V_X7R",3200,3000,"+24V_RAW","GND")
two_pin_v("Device:C","C10","100nF_BOOT",2200,4050,"BUCK_BOOT","BUCK_SW")
two_pin_v("Device:D","D4","SS110_100V",2800,4050,"GND","BUCK_SW")
conn1("L1","FNR6045S220MT_22uH",3500,1750,2,["BUCK_SW","+3V3"])
two_pin_v("Device:C","C11","22uF_25V_X5R",3700,2600,"+3V3","GND")
two_pin_v("Device:C","C15","22uF_25V_X5R",4200,2600,"+3V3","GND")
two_pin_v("Device:R","R12","100k_1%_FB_TOP",3200,3900,"BUCK_FB","+3V3")
two_pin_v("Device:R","R13","29.4k_1%_FB_BOTTOM",3700,3900,"BUCK_FB","GND")
two_pin_v("Device:R","R14","49.9k_1%_RT_500kHz",4200,3900,"BUCK_RT","GND")
# 3V3 bulk/local decoupling is shown beside the ESP32 block to avoid dense
# passive-column wire collisions in the buck drawing.
two_pin_v("Device:C","C7","100nF_U4_3V3_OUT",12300,1500,"+3V3","GND")
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box(4700,950,9000,4600); note(4850,1120,"FAN GATE DRIVER + EXTERNAL SSR DRIVER",70)
conn1("J2","24V_FAN_OUTPUT",5000,1600,2,["+24V_RAW","FAN_NEG"])
conn1("U6","UCC27511DBVR",5750,1700,6,["VDRV10","FAN_GATE_ON","FAN_GATE_OFF","GND","GND","FAN_PWM"])
two_pin_h("Device:R","R1","100R_GATE_TURN_ON",6500,1350,"FAN_GATE_ON","FAN_GATE")
two_pin_h("Device:R","R15","10R_GATE_TURN_OFF",6500,1950,"FAN_GATE_OFF","FAN_GATE")
two_pin_v("Device:R","R2","100k_GATE_PULLDOWN",7300,2600,"FAN_GATE","GND")
conn1("Q1","STP55NF06L_GDS",7300,1650,3,["FAN_GATE","FAN_NEG","GND"])
# Device:D vertical rotation maps lower label to pin 1 (K); cathode is +24 V.
two_pin_v("Device:D","D1","SS56-E3/57T_FLYBACK",7900,1650,"FAN_NEG","+24V_RAW")
two_pin_v("Device:D_TVS","D3","SMBJ33A_FAN_TVS",8500,1650,"FAN_NEG","+24V_RAW")
two_pin_v("Device:R","R16","2.7k_1%_250mW",5000,3000,"+24V_RAW","VDRV10")
two_pin_v("Device:D_Zener","D5","BZT52C10_10V",5600,3000,"GND","VDRV10")
two_pin_v("Device:C","C13","1uF_25V_VDRV",6200,3000,"VDRV10","GND")
two_pin_v("Device:C","C14","100nF_50V_VDRV",6800,3000,"VDRV10","GND")
conn1("J3","EXTERNAL_SSR_INPUT_3V3",5000,4000,2,["+3V3","SSR_NEG"])
two_pin_h("Device:R","R3","100R",6000,3900,"HEATER_PWM","SSR_GATE")
two_pin_v("Device:R","R4","100k_GATE_PULLDOWN",6700,4100,"SSR_GATE","GND")
conn1("Q2","2N7002_SSR_DRIVER_GDS",7500,4000,3,["SSR_GATE","GND","SSR_NEG"])
note(8050,4300,"SSR input only — no mains on PCB",45)

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two_pin_h("Switch:SW_Push","SW1","RESET",10100,4300,"EN","GND")
two_pin_h("Device:R","R6","10k_BOOT_PULLUP",11000,4000,"+3V3","BOOT")
two_pin_h("Switch:SW_Push","SW2","BOOT",11500,4300,"BOOT","GND")
conn1("JGPIO1","SPARE_GPIO_BREAKOUT",12600,3900,6,["GPIO3","GPIO46","GPIO9","GPIO10","GPIO48","GPIO45"])
conn1("J6","ESC_24V_GND_PWM_GND_GPIO10",14600,4200,4,["+24V_RAW","GND","GPIO10","GND"])
note(13700,4750,"ESC connector pin order: +24V / GND / PWM(GPIO10) / GND",45)
# Schematic-only anchor for nets that exist solely on PCB probe/solder pads.
# No footprint is assigned; TPESP/PADESP are intentionally board-only objects.
conn1("JDEBUGSCHEM1","PCB_ONLY_DEBUG_NET_ANCHOR",14500,2700,23,[
    "U4_PGOOD_NC","GPIO4","GPIO5","GPIO6","GPIO7","GPIO15","GPIO16","GPIO17","GPIO18","GPIO8",
    "GPIO14","GPIO21","GPIO47","GPIO35","GPIO36","GPIO37","GPIO38","GPIO39","GPIO40","GPIO41",
    "GPIO42","RXD0_GPIO44","TXD0_GPIO43"
], fp="")

# Thermocouple interface
box(500,4900,4500,7300); note(650,5070,"K-TYPE THERMOCOUPLE / MAX6675",70)
conn1("J4","K_TYPE_THERMOCOUPLE",900,5900,2,["THERMO_PLUS","THERMO_MINUS"])
two_pin_v("Device:C","C5","1nF_C0G_DNP_IF_BIASED",1600,5900,"THERMO_PLUS","THERMO_MINUS")
conn1("U2","MAX6675_SOIC8_3V3",2900,5900,8,["GND","THERMO_MINUS","THERMO_PLUS","+3V3","MAX_SCK","MAX_CS","MAX_DO","GND"])
two_pin_v("Device:C","C3","100nF_MAX6675",3900,5900,"+3V3","GND")
note(700,6900,"Firmware: DO=GPIO11, CS=GPIO12, SCK=GPIO13",50)
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# USB-C data-only interface and ESD
box(4700,4900,9000,7300); note(4850,5070,"USB-C DATA / FLASH (VBUS SENSE ONLY)",70)
conn1("J5","USB_C_RECEPTACLE_USB2",5100,6000,8,["GND","USB_VBUS","USB_CC1","USB_DP","USB_DN","USB_CC2","USB_VBUS","GND"])
two_pin_v("Device:R","R10","5.1k_CC1_RD",6000,5400,"USB_CC1","GND")
two_pin_v("Device:R","R11","5.1k_CC2_RD",6700,5400,"USB_CC2","GND")
two_pin_h("Device:R","R7","27R_USB_DN",6300,6400,"USB_DN_MCU","USB_DN")
two_pin_h("Device:R","R8","27R_USB_DP",6300,6800,"USB_DP_MCU","USB_DP")
conn1("U5","USBLC6-2SC6_USB_ESD",8000,6100,6,["USB_DN","GND","USB_DP","USB_DP","USB_VBUS","USB_DN"])
note(5000,7100,"USB VBUS does not power the controller",45)

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
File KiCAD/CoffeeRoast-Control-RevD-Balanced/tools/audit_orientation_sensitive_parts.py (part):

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    "J4": {"1": "THERMO_PLUS", "2": "THERMO_MINUS"},
    "J5": {"1": "GND", "2": "USB_VBUS", "3": "USB_CC1", "4": "USB_DP",
           "5": "USB_DN", "6": "USB_CC2", "7": "USB_VBUS", "8": "GND"},
    "J6": {"1": "+24V_RAW", "2": "GND", "3": "GPIO10", "4": "GND"},
    "J7": {"1": "+3V3", "2": "GND", "3": "GPIO4", "4": "GPIO5",
           "5": "GPIO6", "6": "GPIO7"},
    "J8": {"1": "+3V3", "2": "GND", "3": "GPIO8", "4": "GPIO9",
           "5": "GPIO14", "6": "GPIO21"},
    "J9": {"1": "GND", "2": "GPIO15", "3": "GPIO16", "4": "GPIO17",
           "5": "GPIO18", "6": "+3V3"},
    "JGPIO1": {"1": "GPIO3", "2": "GPIO46", "3": "GPIO9", "4": "GPIO10",
               "5": "GPIO48", "6": "GPIO45"},
    "U1": {"1": "GND", "2": "+3V3", "3": "EN", "4": "GPIO4", "5": "GPIO5",
           "6": "GPIO6", "7": "GPIO7", "8": "GPIO15", "9": "GPIO16",
           "10": "GPIO17", "11": "GPIO18", "12": "GPIO8", "13": "USB_DN_MCU",
           "14": "USB_DP_MCU", "15": "GPIO3", "16": "GPIO46", "17": "GPIO9",
           "18": "GPIO10", "19": "MAX_DO", "20": "MAX_CS", "21": "MAX_SCK",
           "22": "GPIO14", "23": "GPIO21", "24": "GPIO47", "25": "GPIO48",
           "26": "GPIO45", "27": "BOOT", "28": "GPIO35", "29": "GPIO36",
           "30": "GPIO37", "31": "GPIO38", "32": "GPIO39", "33": "GPIO40",
           "34": "GPIO41", "35": "GPIO42", "36": "RXD0_GPIO44",
           "37": "TXD0_GPIO43", "38": "FAN_PWM", "39": "HEATER_PWM", "40": "GND"},
    "U2": {"1": "GND", "2": "THERMO_MINUS", "3": "THERMO_PLUS", "4": "+3V3",
           "5": "MAX_SCK", "6": "MAX_CS", "7": "MAX_DO", "8": "GND"},
    "U4": {"1": "BUCK_BOOT", "2": "+24V_RAW", "3": "+24V_RAW", "4": "BUCK_RT",
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
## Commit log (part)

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2025-03-27 initial commit^
2025-03-27 Readme added
2025-05-18 added schaltplan.png yw
2025-05-18 added recipes
2025-05-18 readme update
2025-05-18 adjusted some values for more precise roasting
2025-05-31 adding image to readme
2025-05-31 Update README.md
    fixed and typos
2025-05-31 adding image to readme (#1)
    * adding image to readme
    * Update README.md
    fixed and typos
2025-05-31 changes during testing at BK
2025-05-31 add ui screenshot
2025-05-31 adding video
2025-06-01 removed all the typos
2025-06-03 maximum runtime increased to 20min. fixed crash after running out of roasting profile
2025-06-15 adding peanut profile, adding gitignore for visual studio
2025-06-15 button shows state
2025-06-15 commented out debugging lines
2025-06-15 implemented failsafe after 20 error temperature readings
2025-06-15 invalid readings do not contribute to PID
2025-06-15 more debugging options and time multiplicator added
2025-06-16 bugfix
2025-06-18 bugfix. restarting a profile did not work
2025-10-26 Fix roast preparation crashes and improve cooling handling
2026-04-14 project: Updated 'CoffeeRoast'
2026-04-14 ticket: Updated 'Fix control loop timer interval scaling'
2026-04-14 ticket: Updated 'Document how to build and run the Windows control application'
2026-04-17 ticket: Created 'Rework UI' [improvement/high]
2026-04-18 ticket: Updated 'Add bounds checks before writing PID history arrays'
2026-04-25 implemented best practices
